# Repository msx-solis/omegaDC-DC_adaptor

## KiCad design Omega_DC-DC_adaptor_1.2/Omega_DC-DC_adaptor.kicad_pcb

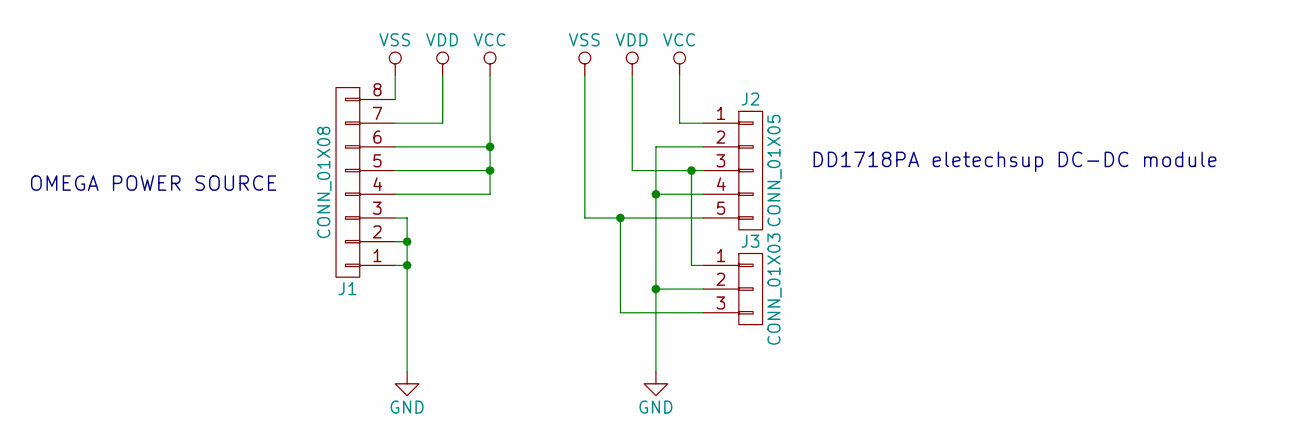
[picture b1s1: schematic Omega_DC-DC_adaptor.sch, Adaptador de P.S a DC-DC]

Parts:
J1: CONN_01X08; Pin_Header_Straight_1x08_Pitch2.54mm
J2: CONN_01X05; Pin_Header_Straight_1x05_Pitch2.54mm
J3: CONN_01X03; Pin_Header_Angled_1x03_Pitch2.54mm

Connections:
GND: J1.1, J1.2, J1.3, J2.2, J2.4, J3.2
VCC: J1.4, J1.5, J1.6, J2.1
VDD: J1.7, J2.3, J3.1
VSS: J1.8, J2.5, J3.3

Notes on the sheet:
OMEGA POWER SOURCE
DD1718PA eletechsup DC-DC module

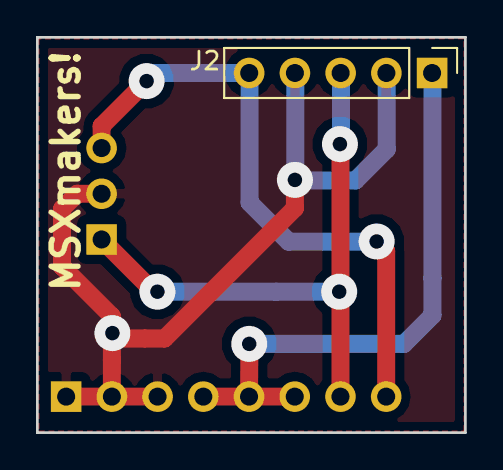
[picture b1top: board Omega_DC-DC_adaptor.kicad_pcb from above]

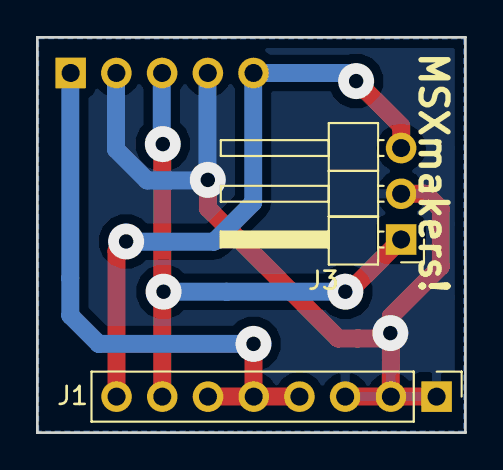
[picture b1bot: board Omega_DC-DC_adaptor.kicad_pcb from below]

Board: 2 copper layers, 23.8 x 22.0 mm, 3 parts (2 on the bottom side), 4 nets.

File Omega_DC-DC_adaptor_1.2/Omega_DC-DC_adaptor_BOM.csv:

Reference, Value, Footprint, Datasheet
"J1","CONN_01X08","Pin_Headers:Pin_Header_Straight_1x08_Pitch2.54mm",""
"J2","CONN_01X05","Pin_Headers:Pin_Header_Straight_1x05_Pitch2.54mm",""
"J3","CONN_01X03","Pin_Headers:Pin_Header_Angled_1x03_Pitch2.54mm",""
